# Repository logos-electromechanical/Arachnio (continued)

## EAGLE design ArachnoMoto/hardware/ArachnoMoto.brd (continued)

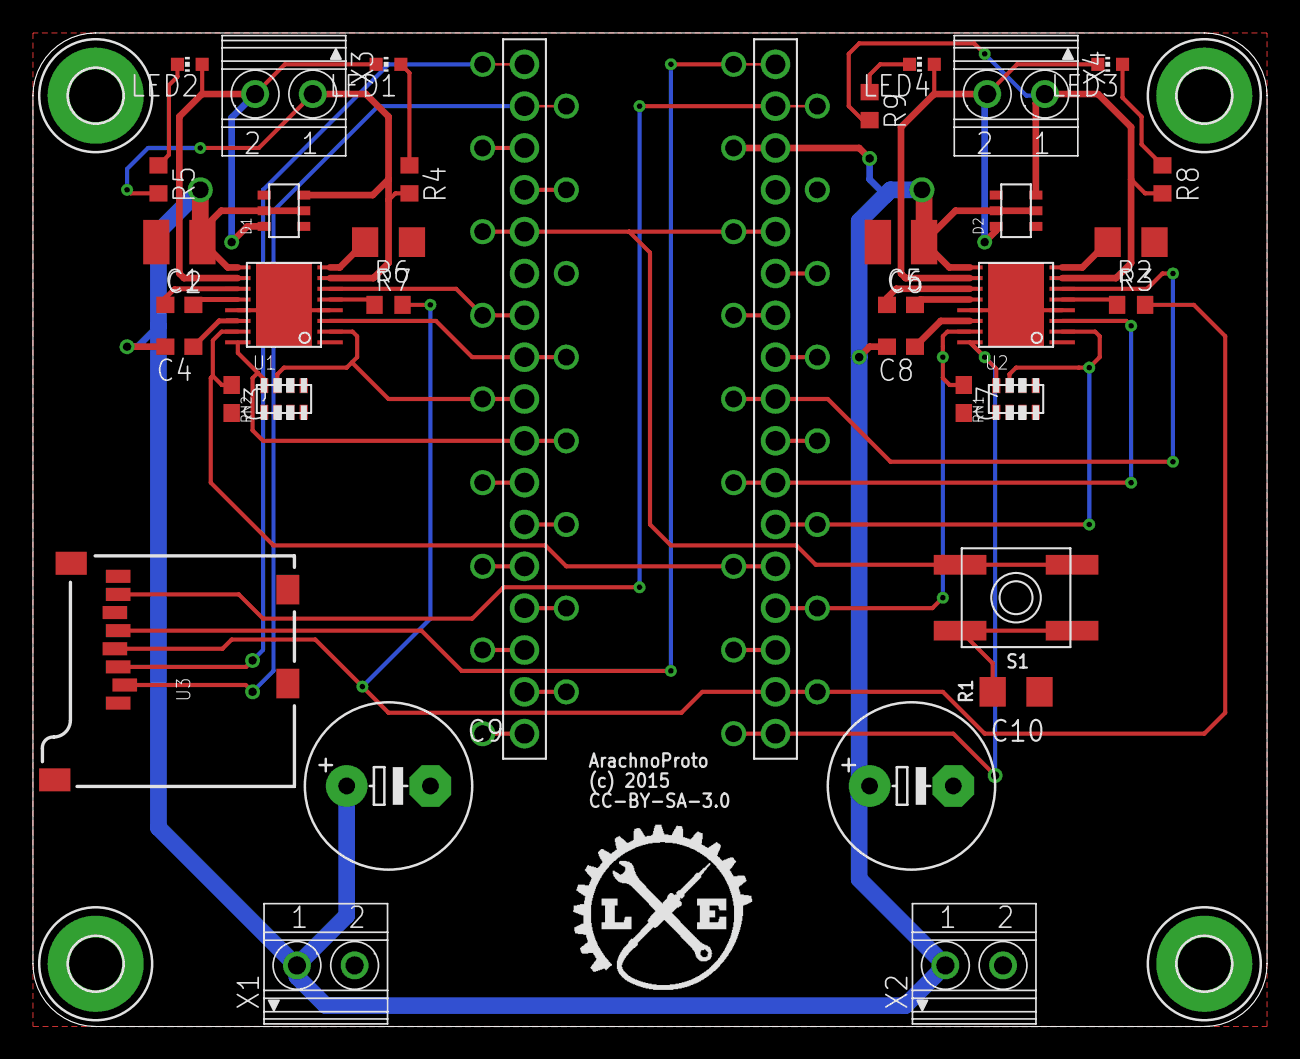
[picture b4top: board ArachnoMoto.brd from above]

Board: 2 copper layers, 74.9 x 60.3 mm, 42 parts (0 on the bottom side), 51 nets.

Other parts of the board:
U$1: LOGO-SM

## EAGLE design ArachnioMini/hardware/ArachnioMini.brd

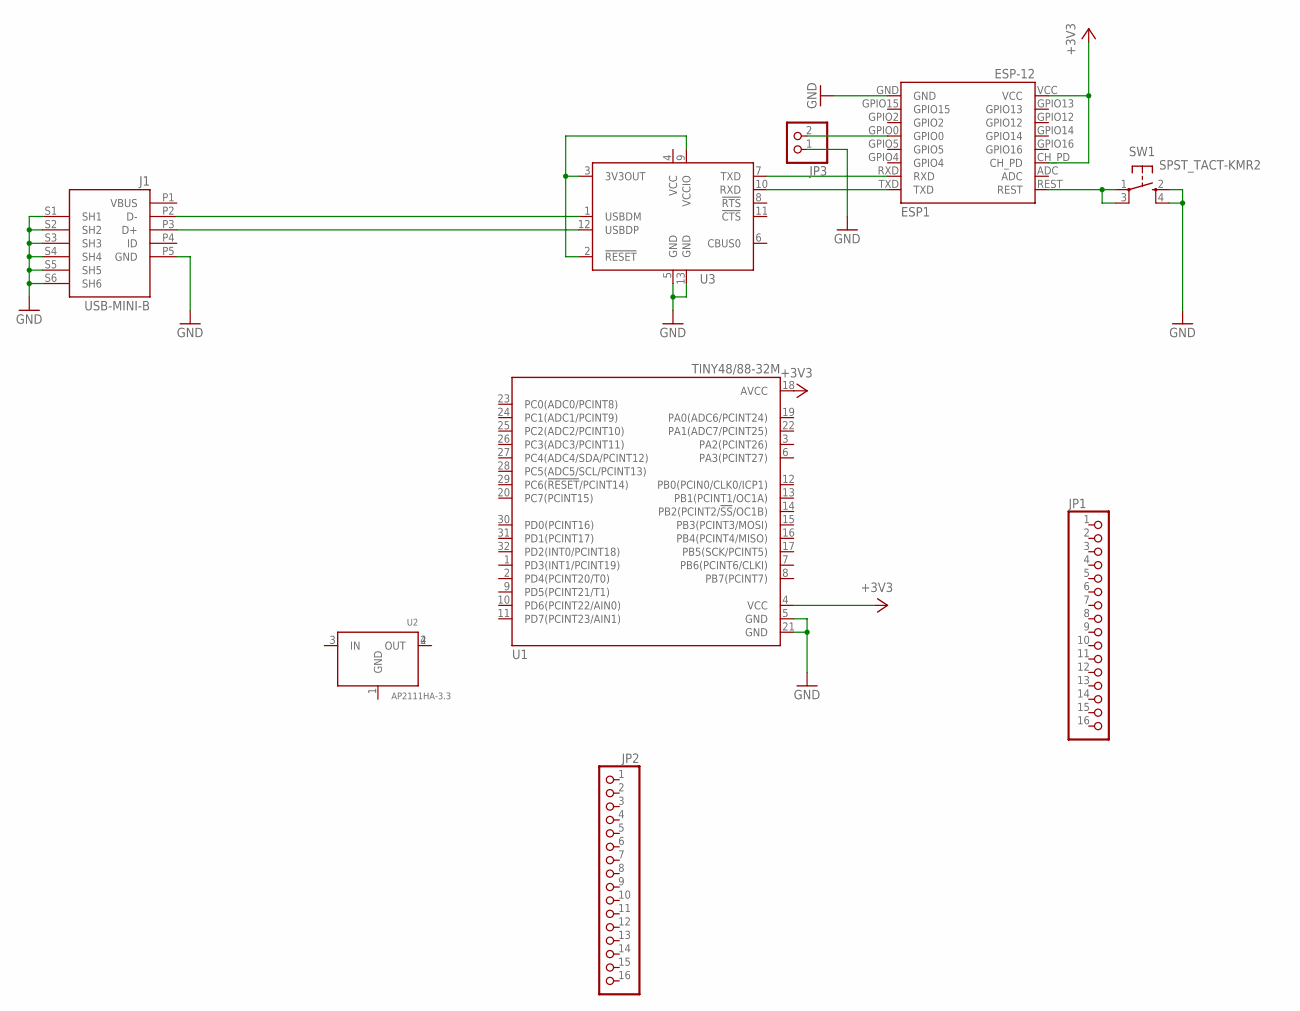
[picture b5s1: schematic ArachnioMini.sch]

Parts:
ESP1: ESP-12
J1: USB-MINI-B; SMARTPRJ_CON2_USB_MICRO_B_AT
JP1, JP2: PINHD-1X16; 1X16
JP3: PINHD-1X2; 1X02
SW1: SPST_TACT-KMR2; KMR2
U1: TINY48/88-32M; MLF32
U2: AP2111HA-3.3; SOT223
U3: FT234XD; DFN12

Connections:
+3V3: ESP1.CH_PD, ESP1.VCC, U1.4 (VCC), U1.18 (AVCC)
GND: ESP1.GND, J1.P5 (GND), J1.S1 (SH1), J1.S2 (SH2), J1.S3 (SH3), J1.S4 (SH4), J1.S5 (SH5), J1.S6 (SH6), JP3.1, SW1.2 (S), SW1.4 (S1), U1.5 (GND), U1.21 (GND), U3.5 (GND), U3.13 (GND)
unnamed: ESP1.TXD, U3.10 (RXD)
unnamed: ESP1.RXD, U3.7 (TXD)
unnamed: U3.2 (!RESET!), U3.3 (3V3OUT), U3.9 (VCCIO)
unnamed: J1.P3 (D+), U3.12 (USBDP)
unnamed: J1.P2 (D-), U3.1 (USBDM)
unnamed: ESP1.GPIO0, JP3.2
unnamed: ESP1.REST, SW1.1, SW1.3 (P1)
VBUS: J1.P1 (VBUS)

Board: 2 copper layers, 9 parts (0 on the bottom side), 9 nets, no tracks yet.

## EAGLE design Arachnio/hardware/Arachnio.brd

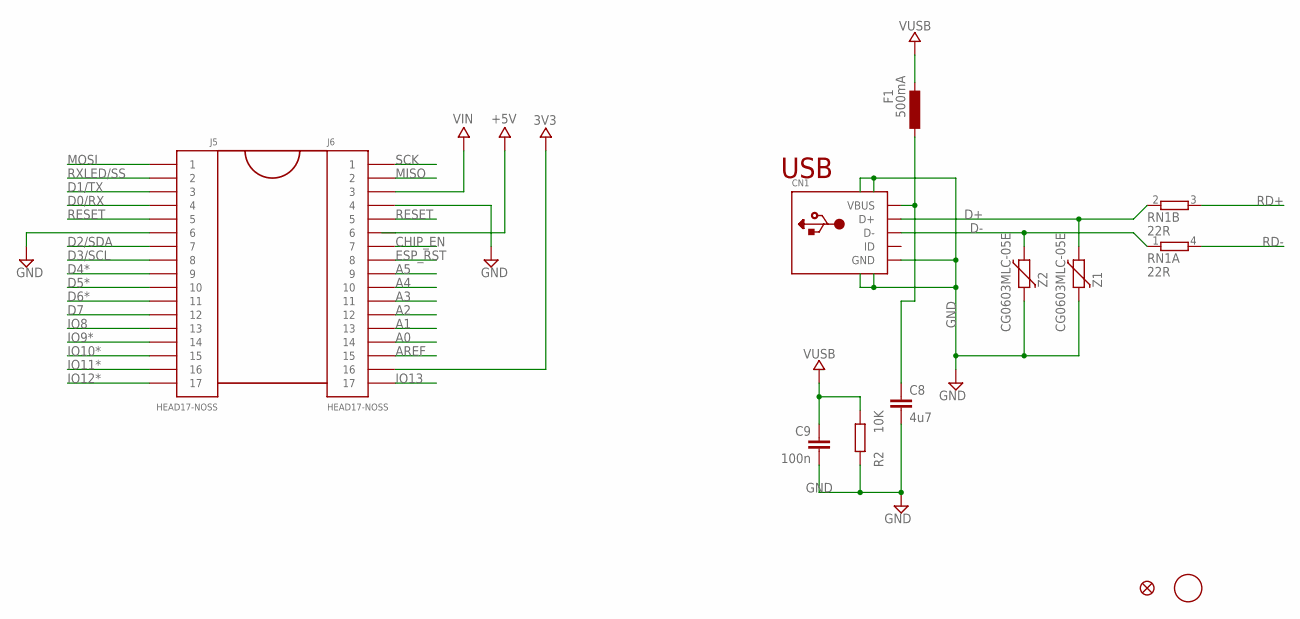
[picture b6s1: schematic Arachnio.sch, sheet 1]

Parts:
C8: 4u7; C0603; PARTNO CL10A475KA8NQNC
C9: 100n; C0603; PARTNO CC0603ZRY5V9BB104
CN1: USBMINIB; USB-MINIB; PARTNO USB-M26FTR
F1: 500mA; L1812; PARTNO MF-MSMF050-2
J5: HEAD17-NOSS; PARTNO PREC017SAAN-RC
J6: HEAD17-NOSS; HEAD17-NOSS-1; PARTNO PREC017SAAN-RC
R2: 10K; R0603; PARTNO RNCP0603FTD10K0
RN1: 22R; EXBV4V; PARTNO EXB-V4V220JV
U$37: FIDUCIALMOUNT; FIDUCIA-MOUNT
U$53: FIDUCIAL1X2; FIDUCIAL-1X2
Z1, Z2: CG0603MLC-05E; CT/CN0603; PARTNO CG0603MLC-05E

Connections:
3V3: J6.16; also elsewhere on the board
+5V: J6.6; also elsewhere on the board
A0: J6.14; also elsewhere on the board
A1: J6.13; also elsewhere on the board
A2: J6.12; also elsewhere on the board
A3: J6.11; also elsewhere on the board
A4: J6.10; also elsewhere on the board
A5: J6.9; also elsewhere on the board
AREF: J6.15; also elsewhere on the board
CHIP_EN: J6.7; also elsewhere on the board
D0/RX: J5.4; also elsewhere on the board
D1/TX: J5.3; also elsewhere on the board
D2/SDA: J5.7; also elsewhere on the board
D3/SCL: J5.8; also elsewhere on the board
D4*: J5.9; also elsewhere on the board
D5*: J5.10; also elsewhere on the board
D6*: J5.11; also elsewhere on the board
D7: J5.12; also elsewhere on the board
D+: CN1.D+, RN1.2 (1), Z1.1
D-: CN1.D-, RN1.1, Z2.1
ESP_RST: J6.8; also elsewhere on the board
GND: C8.2, C9.2, CN1.GND, CN1.GND1 (SHIELD), CN1.GND2 (SHIELD), CN1.GND3 (SHIELD), CN1.GND4 (SHIELD), J5.6, J6.4, R2.1, Z1.2, Z2.2; also elsewhere on the board
IO8: J5.13; also elsewhere on the board
IO9*: J5.14; also elsewhere on the board
IO10*: J5.15; also elsewhere on the board
IO11*: J5.16; also elsewhere on the board
IO12*: J5.17; also elsewhere on the board
IO13: J6.17; also elsewhere on the board
MISO: J6.2; also elsewhere on the board
MOSI: J5.1; also elsewhere on the board
RD+: RN1.3 (2); also elsewhere on the board
RD-: RN1.4 (2); also elsewhere on the board
RESET: J5.5, J6.5; also elsewhere on the board
RXLED/SS: J5.2; also elsewhere on the board
SCK: J6.1; also elsewhere on the board
VIN: J6.3; also elsewhere on the board
VUSB: C9.1, F1.2, R2.2; also elsewhere on the board
VUSBD: C8.1, CN1.VBUS, F1.1

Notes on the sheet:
USB

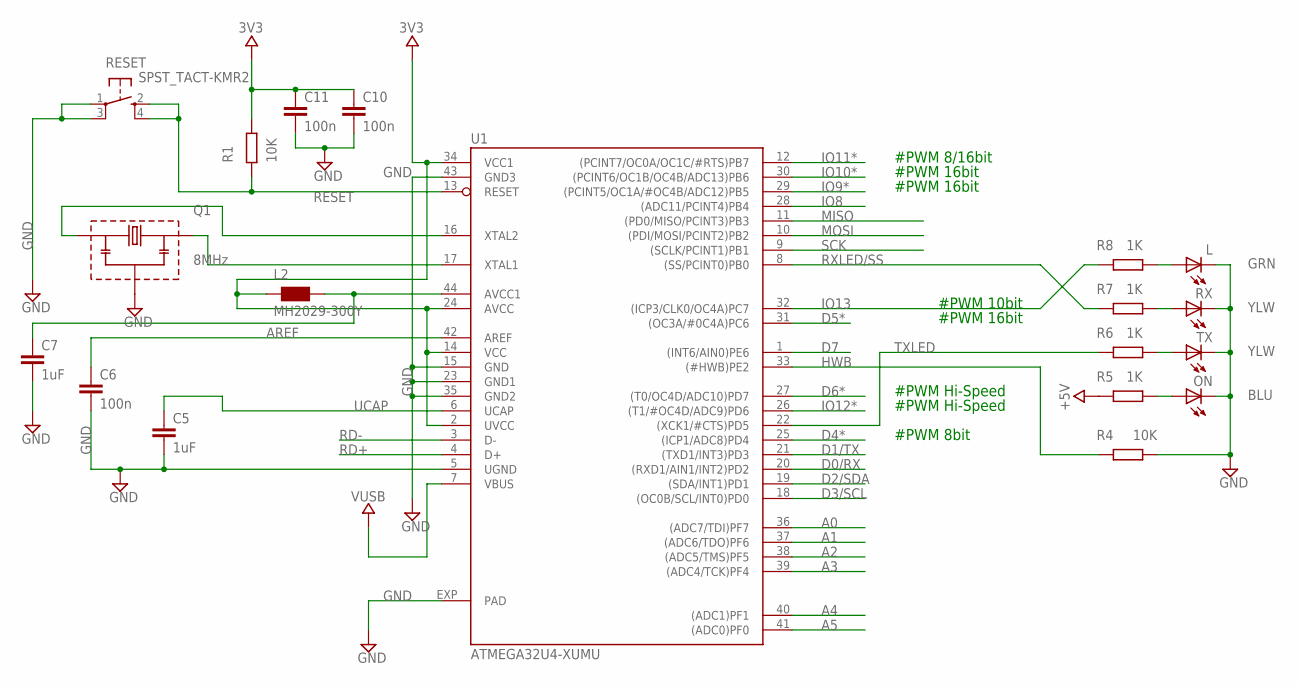
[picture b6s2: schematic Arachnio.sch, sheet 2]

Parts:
C5, C7: 1uF; C0603; PARTNO C0603C105K3PACTU
C6, C10, C11: 100n; C0603; PARTNO CC0603ZRY5V9BB104
L: GRN; CHIP-LED0603; PARTNO LTST-C191KGKT
L2: MH2029-300Y; 0805; PARTNO MH2029-300Y
ON: BLU; CHIP-LED0603; PARTNO LB Q39G-L2N2-35-1
Q1: 8MHz; PRQC; PARTNO PRQC8.00CR1010V00L
R1, R4: 10K; R0603; PARTNO RNCP0603FTD10K0
R5, R6, R7, R8: 1K; R0603; PARTNO RMCF0603FT1K00
RESET: SPST_TACT-KMR2; KMR2; PARTNO KMR221NG
RX: YLW; CHIP-LED0603; PARTNO LTST-C191KSKT
TX: YLW; CHIP-LED0603; PARTNO LTST-C191KSKT
U1: ATMEGA32U4-XUMU; QFN44ML7X7; PARTNO ATMEGA32U4-MU

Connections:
3V3: C10.1, C11.1, L2.1, R1.1, U1.2 (UVCC), U1.14 (VCC), U1.24 (AVCC), U1.34 (VCC1); also elsewhere on the board
+5V: R5.1; also elsewhere on the board
A0: U1.36 ((ADC7/TDI)PF7); also elsewhere on the board
A1: U1.37 ((ADC6/TDO)PF6); also elsewhere on the board
A2: U1.38 ((ADC5/TMS)PF5); also elsewhere on the board
A3: U1.39 ((ADC4/TCK)PF4); also elsewhere on the board
A4: U1.40 ((ADC1)PF1); also elsewhere on the board
A5: U1.41 ((ADC0)PF0); also elsewhere on the board
AREF: C6.1, U1.42 (AREF); also elsewhere on the board
AVCC: C7.1, L2.2, U1.44 (AVCC1)
D0/RX: U1.20 ((RXD1/AIN1/INT2)PD2); also elsewhere on the board
D1/TX: U1.21 ((TXD1/INT3)PD3); also elsewhere on the board
D2/SDA: U1.19 ((SDA/INT1)PD1); also elsewhere on the board
D3/SCL: U1.18 ((OC0B/SCL/INT0)PD0); also elsewhere on the board
D4*: U1.25 ((ICP1/ADC8)PD4); also elsewhere on the board
D5*: U1.31 ((OC3A/#0C4A)PC6); also elsewhere on the board
D6*: U1.27 ((T0/OC4D/ADC10)PD7); also elsewhere on the board
D7: U1.1 ((INT6/AIN0)PE6); also elsewhere on the board
GND: C5.2, C6.2, C7.2, C10.2, C11.2, L.C, ON.C, Q1.P$2 (2), R4.2, RESET.1, RESET.3 (P1), RX.C, TX.C, U1.5 (UGND), U1.15 (GND), U1.23 (GND1), U1.35 (GND2), U1.43 (GND3), U1.EXP (PAD); also elsewhere on the board
HWB: R4.1, U1.33 ((#HWB)PE2)
IO8: U1.28 ((ADC11/PCINT4)PB4); also elsewhere on the board
IO9*: U1.29 ((PCINT5/OC1A/#OC4B/ADC12)PB5); also elsewhere on the board
IO10*: U1.30 ((PCINT6/OC1B/OC4B/ADC13)PB6); also elsewhere on the board
IO11*: U1.12 ((PCINT7/OC0A/OC1C/#RTS)PB7); also elsewhere on the board
IO12*: U1.26 ((T1/#OC4D/ADC9)PD6); also elsewhere on the board
IO13: R8.1, U1.32 ((ICP3/CLK0/OC4A)PC7); also elsewhere on the board
MISO: U1.11 ((PD0/MISO/PCINT3)PB3); also elsewhere on the board
MOSI: U1.10 ((PDI/MOSI/PCINT2)PB2); also elsewhere on the board
unnamed: R7.2, RX.A
unnamed: ON.A, R5.2
unnamed: R6.2, TX.A
unnamed: L.A, R8.2
RD+: U1.4 (D+); also elsewhere on the board
RD-: U1.3 (D-); also elsewhere on the board
RESET: R1.2, RESET.2 (S), RESET.4 (S1), U1.13 (RESET); also elsewhere on the board
RXLED/SS: R7.1, U1.8 ((SS/PCINT0)PB0); also elsewhere on the board
SCK: U1.9 ((SCLK/PCINT1)PB1); also elsewhere on the board
TXLED: R6.1, U1.22 ((XCK1/#CTS)PD5)
UCAP: C5.1, U1.6 (UCAP)
VUSB: U1.7 (VBUS); also elsewhere on the board
XTAL1: Q1.P$3 (3), U1.17 (XTAL1)
XTAL2: Q1.P$1 (1), U1.16 (XTAL2)

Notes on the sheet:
#PWM 8bit
#PWM Hi-Speed
#PWM 16bit
#PWM 10bit
#PWM 8/16bit

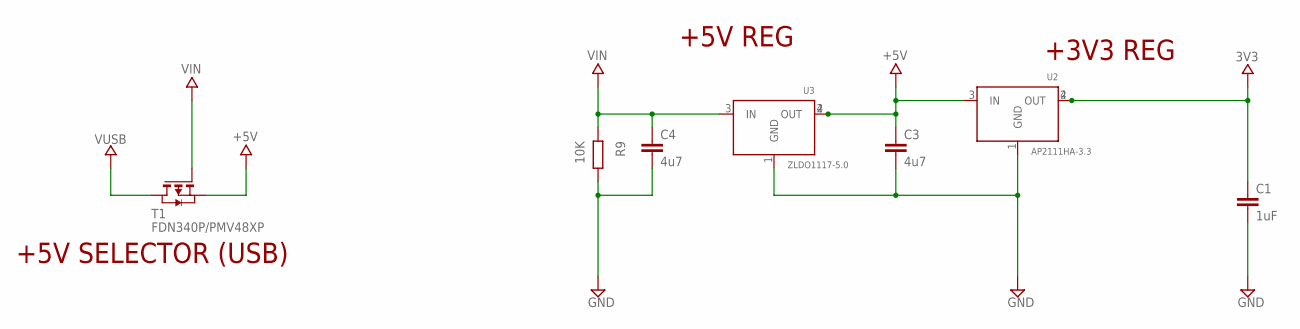
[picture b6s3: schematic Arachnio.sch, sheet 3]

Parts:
C1: 1uF; C0603; PARTNO C0603C105K3PACTU
C3, C4: 4u7; C0603; PARTNO CL10A475KA8NQNC
R9: 10K; R0603; PARTNO RNCP0603FTD10K0
T1: FDN340P/PMV48XP; SOT-23; PARTNO FDN340P
U2: AP2111HA-3.3; SOT223; PARTNO AP2111H-3.3TRG1
U3: ZLDO1117-5.0; SOT223

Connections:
3V3: C1.1, U2.2 (OUT), U2.4 (OUT); also elsewhere on the board
+5V: C3.1, T1.2 (S), U2.3 (IN), U3.2 (OUT), U3.4 (OUT); also elsewhere on the board
GND: C1.2, C3.2, C4.2, R9.1, U2.1 (GND), U3.1 (GND); also elsewhere on the board
VIN: C4.1, R9.2, T1.3 (G), U3.3 (IN); also elsewhere on the board
VUSB: T1.1 (D); also elsewhere on the board

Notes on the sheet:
+5V REG
+5V SELECTOR (USB)
+3V3 REG

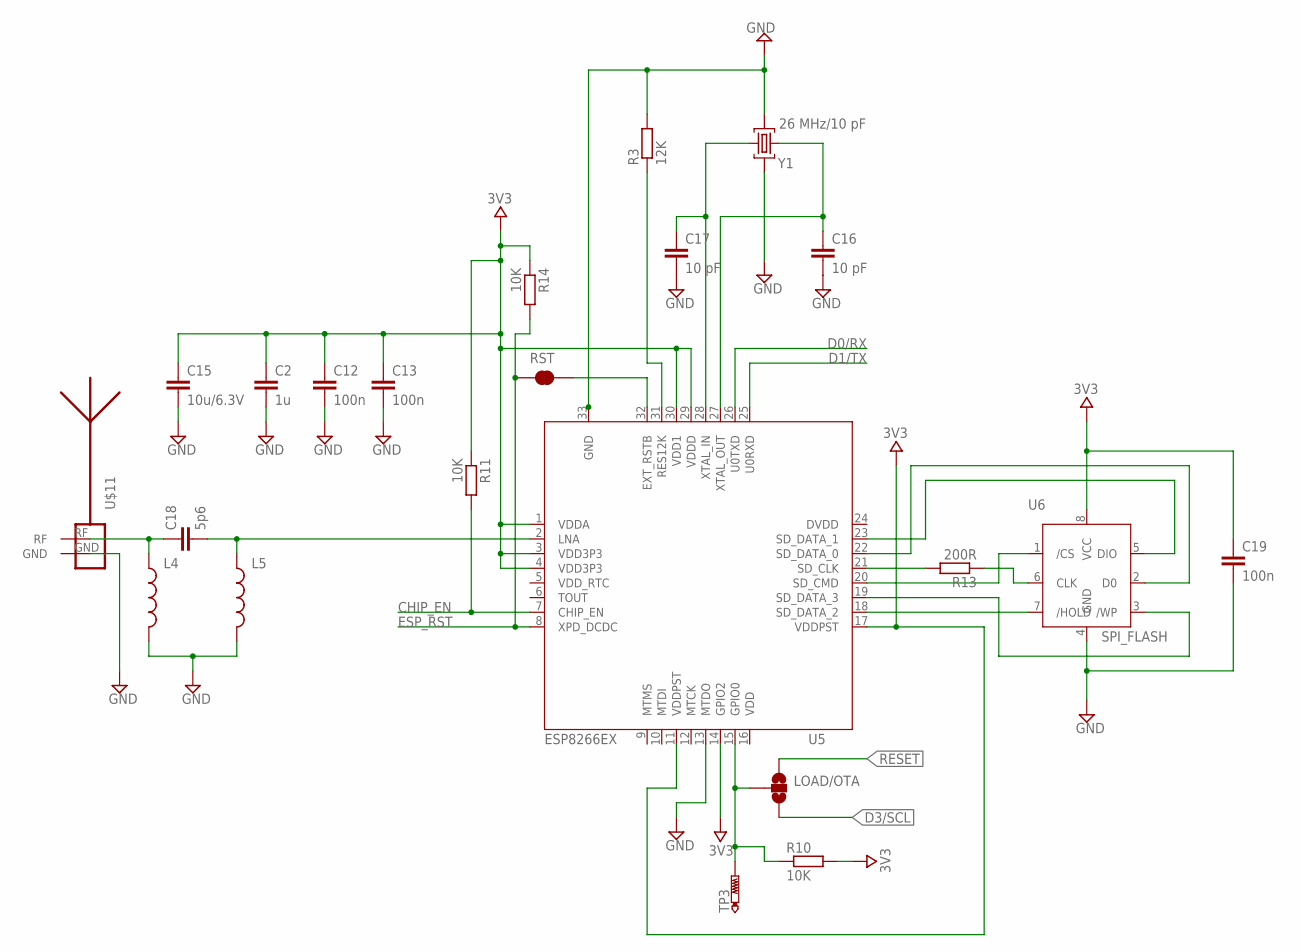
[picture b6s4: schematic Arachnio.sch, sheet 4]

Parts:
C2: 1u; C0603; PARTNO C0603C105K3PACTU
C12, C13, C19: 100n; C0603; PARTNO CC0603ZRY5V9BB104
C15: 10u/6.3V; C0603; PARTNO JMK107ABJ106MAHT
C16, C17: 10 pF; C0603; PARTNO C0603C100K5GACTU
C18: 5p6; C0603; PARTNO 251R14S5R6CV4T
L4, L5: INDUCTOR0603; 0603
LOAD/OTA: JUMPER-PAD-3-NOYES_SILK; PAD-JUMPER-3-NO_YES_SILK
R3: 12K; R0603; PARTNO RMCF0603FT12K0
R10, R11, R14: 10K; R0603; PARTNO RNCP0603FTD10K0
R13: 200R; R0603; PARTNO MCR03ERTJ201
RST: JUMPER-PAD-2-NC_BY_TRACE; PAD-JUMPER-2-NC_BY_TRACE_YES_SILK
TP3: PTR1TP15SQ; TP15SQ
U5: ESP8266EX; QFN32; PARTNO ESP8266EX
U6: SPI_FLASH; SOIC-8; PARTNO SST25VF512A-33-4C-SAE
U$11: ANTENNA_1RIGHT; SWRA117D_RIGHT; PARTNO *
Y1: 26 MHz/10 pF; CRYSTAL-3.2-2.5; PARTNO 403C11A26M00000

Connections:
3V3: C2.1, C12.1, C13.1, C15.1, C19.1, R10.2, R11.1, R14.1, U5.1 (VDDA), U5.3 (VDD3P3), U5.4 (VDD3P3), U5.11 (VDDPST), U5.14 (GPIO2), U5.17 (VDDPST), U5.29 (VDDD), U5.30 (VDD1), U6.8 (VCC); also elsewhere on the board
CHIP_EN: R11.2, U5.7 (CHIP_EN); also elsewhere on the board
D0/RX: U5.26 (U0TXD); also elsewhere on the board
D1/TX: U5.25 (U0RXD); also elsewhere on the board
D3/SCL: LOAD/OTA.3; also elsewhere on the board
DVDD: U5.24 (DVDD)
ESP_RST: R14.2, RST.1, U5.8 (XPD_DCDC); also elsewhere on the board
GND: C2.2, C12.2, C13.2, C15.2, C16.2, C17.2, C19.2, L4.2, L5.2, R3.2, U5.13 (MTDO), U5.33 (GND), U6.4 (GND), U$11.GND, Y1.2 (GND), Y1.4 (GND); also elsewhere on the board
unnamed: LOAD/OTA.2, R10.1, TP3.TP, U5.15 (GPIO0)
unnamed: C17.1, U5.28 (XTAL_IN), Y1.1 (C1)
unnamed: C16.1, U5.27 (XTAL_OUT), Y1.3 (C2)
unnamed: C18.1, L4.1, U$11.RF
unnamed: R3.1, U5.31 (RES12K)
unnamed: RST.2, U5.32 (EXT_RSTB)
unnamed: R13.2, U5.21 (SD_CLK)
unnamed: R13.1, U6.6 (CLK)
unnamed: U5.20 (SD_CMD), U6.1 (/CS)
unnamed: U5.18 (SD_DATA_2), U6.7 (/HOLD)
unnamed: U5.19 (SD_DATA_3), U6.3 (/WP)
unnamed: U5.23 (SD_DATA_1), U6.5 (DIO)
unnamed: U5.22 (SD_DATA_0), U6.2 (D0)
unnamed: C18.2, L5.1, U5.2 (LNA)
RESET: LOAD/OTA.1; also elsewhere on the board
VDD: U5.16 (VDD)
VDD_RTC: U5.5 (VDD_RTC)

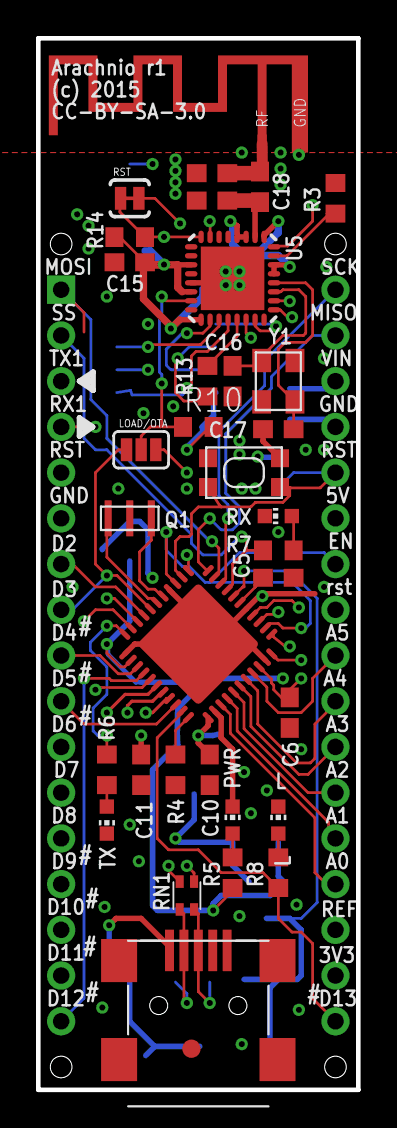
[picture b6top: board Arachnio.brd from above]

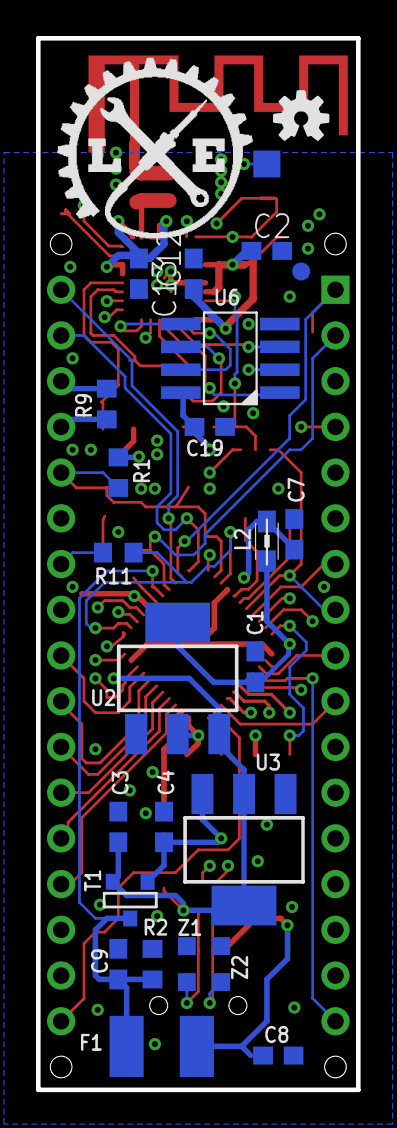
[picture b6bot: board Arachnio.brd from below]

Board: 4 copper layers, 17.8 x 58.4 mm, 62 parts (26 on the bottom side), 62 nets.

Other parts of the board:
U$1: LOGO-SM
U$12: OSHW-LOGO-S

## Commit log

2015-03-20 .\2ipabdrn.paw.txt
2015-03-22 -- Re-arranged Arachnode to solve connector interference. -- Created pinout diagrams for Arachnio -- Added sketch for serial console
2015-03-22 -- Fixed missing parts designators in silkscreen
2015-03-22 -- Added mounting pads on the board -- Made reset button an independent button -- Changed all components to SMD
2015-03-22 Sometimes eagle is silly...
2015-03-25 .\jb1jai5l.nmn.txt
2015-03-25 ﻿-- added power switching to make USB power work correctly. # Please enter the commit message for your changes. Lines starting # with '#' will be ignored, and an empty message aborts the commit. # On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
2015-04-03 ﻿pretty pictures # Please enter the commit message for your changes. Lines starting # with '#' will be ignored, and an empty message aborts the commit. # On branch master # Your branch is up-to-date 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
2015-04-11 ﻿Deleted an improper airwire # Please enter the commit message for your changes. Lines starting # with '#' will be ignored, and an empty message aborts the commit. # On branch master # Your branch is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
2015-04-12 ﻿Added 3 new decoupling caps to the ESP8266 # Please enter the commit message for your changes. Lines starting # with '#' will be ignored, and an empty message aborts the commit. # On branch decoupli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
2015-04-12 Fixed upload.params.verbose error
2015-04-12 ﻿Added pull-up commands for GPIO 0 & 2 to enable correct booting This will get a hardware fix on the next board # Please enter the commit message for your changes. Lines starting # with '#' will be i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
2015-04-18 Made some updates while diagnosing prototype issues
2015-04-18 -- Fixed ground plane issues -- Connected USB shield to ground -- Simplified boot select by tying MTDO and GPIO2 low and high, respectively -- Removed test points for MTDO and GPIO2 -- Replaced 0R re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
2015-05-03 Started branch for ArachnioDue (ATSAM3S*A*-MU processor)
2015-05-03 Added a null sketch for flashing code to the ESP via external device
2015-05-03 Checking in last Gerber files for the decoupling branch
2015-05-03 Images of the Arachnode and ArachnoProto release candidates
2015-05-03 -- Checking in sam tree copied from Arduino Due. -- Modified makefiles and boards.txt to accomodate the Arachnio Due (currently UNTESTED!!!) -- Checked in some ESP documentation
2015-05-04 -- Captured schematic for SAM3S*A version
2015-05-14 ﻿First test boards of this design # Please enter the commit message for your changes. Lines starting # with '#' will be ignored, and an empty message aborts the commit. # On branch master # Your bran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
2015-08-19 Pre-prototype check-in
2015-08-19 Modified ArachnoProto to work with the ArachnioDue.
2015-08-19 Modified ArachnNode to Arachnio Due standard
2015-08-20 ArachnoMoto first commit
2015-09-28 Ombnibus commit because I am not sure what I did...
2015-10-09 first module version, ready for mfg
2015-10-09 Checking in zip archive for latest module hardware update
2015-10-17 Moved the Arachnode connectors around for USB clearance.
2015-10-31 Re-arranged features, added test points
2015-10-31 Some last changes to the schematic and layout
2015-10-31 New gerbers for rev 2 module board
2015-10-31 Updated Arachnoproto with fixed SWD header.
2015-10-31 Added Arachnoproto gerbers
2015-11-01 Fixed the Arachnode so it's got triple row headers on the passthroughs
2015-11-01 Fixed broken debug port
2015-11-02 Arachnoproto gerbers
